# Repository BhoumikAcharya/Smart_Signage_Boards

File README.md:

**Modbus-to-MQTT Bridge for Metro Emergency Signage**

> **Reconciled 2026-08-07** against Gateway `Pi.py` v2.0.0 and ESP32 `Firmware.ino` v3.0.0.
> The previous revision (2026-02-17) predated the relay → MOSFET redesign and described hardware and
> a control protocol that no longer exist. See `Embedded/ESP32/DOC_UPDATES_PENDING.md` §10.

**Authoritative documents** — this README is an orientation page; each of these is the source of truth for its area:

| Area | Document |
| --- | --- |
| PLC / SCADA integration | [`Embedded/RaspberryPi/Gateway/SCADA_Integration_Guide.md`](Embedded/RaspberryPi/Gateway/SCADA_Integration_Guide.md) |
| Gateway internals | [`Embedded/RaspberryPi/Gateway/Gateway_doc.md`](Embedded/RaspberryPi/Gateway/Gateway_doc.md) |
| Platform / deployment | [`Embedded/RaspberryPi/pi_agent.md`](Embedded/RaspberryPi/pi_agent.md) |
| ESP32 firmware contract | [`Embedded/ESP32/esp32_contract.md`](Embedded/ESP32/esp32_contract.md) |
| HMI | [`Embedded/RaspberryPi/HMI/hmi_contract.md`](Embedded/RaspberryPi/HMI/hmi_contract.md) |

---

1. Overview Of the Product -

  This project is a smart EROS, designed for reliable operation in public transit environments like metros and railways. It implements a robust communication bridge on a Raspberry Pi, designed to integrate a central industrial control system (using Modbus) with a distributed network of emergency signs (using MQTT), all over **wired Ethernet**. Making the product implemented on a complete local network.

  This architecture allows a PLC or a central control room to instantly and reliably activate or change emergency signage across multiple locations in a station or tunnel, using a combination of industrial-grade protocols and modern IoT technology.

> **There is no wireless link anywhere in this system.** Every ESP32 node reaches the gateway over
> wired Ethernet via a LAN8720 PHY. The nodes have no Wi-Fi credentials and no Wi-Fi code path — the
> ESP32's radio is left off, which is also why only ADC1 is usable for the sensors.

2. System Architecture

  The project is built on a decoupled, hub-and-spoke architecture, which is ideal for critical systems:

  Central Control (PLC/Modbus Master): The primary industrial controller, located in a central control room. It initiates commands by sending standard Modbus "Write Multiple Holding Registers (16(0x10))" requests to the Raspberry Pi.

  2.1. Raspberry Pi (The Bridge & Broker): This is the core of the system and performs three critical roles simultaneously.

  2.2. Modbus TCP Server: A Python script runs continuously, listening for commands from the central controller and updating an internal data model.

  2.3. MQTT Broker: The industry-standard Mosquitto broker runs as a service, managing all communication with the signage units.

  2.4. Industrial HMI: A 10.1" capacitive touch HMI (Waveshare DSI, 1280x800) is connected to the RaspberryPi with manual override.

  2.5. Emergency Signs (ESP32 Clients): Each emergency light signage unit is powered by an ESP32.

  2.6. The ESP32s connect to the Raspberry Pi over Ethernet with a ETH PHY module called the LAN8720 with MQTT communication.

  2.7. They subscribe to specific MQTT topics and wait for commands.

  2.8. They are responsible for the final physical action — driving the LED strips through **10 logic-level N-channel MOSFETs**, switched over I2C by an MCP23017 port expander.

> **The relays are gone.** Earlier revisions of the design switched the signage with 5V dual-channel
> relay modules on GPIO 4/13, and the ESP32 toggled a GPIO directly. The current hardware has no
> relays: the ESP32 talks I2C to an MCP23017 (SDA=GPIO4, SCL=GPIO13) which drives 10 MOSFET gates —
> 5 for the left-hand arrows (Port A0–A4) and 5 for the right (Port B0–B4).
>
> **Only the moving arrows are switched.** The two static zones are hardwired always-on: they are
> current-monitored but can never be commanded on or off.

3. Features -

  3.1. Protocol Bridging: Seamlessly translates industrial-grade Modbus TCP commands into lightweight MQTT messages suitable for the edge nodes.

  3.2. Real-Time, Reliable Control: Uses a multi-threaded approach on the Raspberry Pi to ensure low latency between receiving a Modbus command and publishing the corresponding MQTT message.

  3.3. Scalable: Easily add or remove signage units across a station without any changes to the central controller or bridge logic. The register map is fixed at **100 nodes** (`40001`–`40100`); each sign only needs to know the broker's address and its own register number.

  3.4. Decoupled & Robust: The central controller does not need to know anything about the individual signs, and the signs do not need to know about the controller. This separation makes the system highly reliable and easy to maintain.

  3.5. Custom Logic: The bridge script contains specific control logic, allowing complex actions to be easily implemented.

  3.6. Diagnostics data: Diagnostics data of the LEDs, ESP32 and PSU Failure are communicated through MQTT to the RaspberryPi. Rather than a binary OK/FAIL, each of the four current channels reports a **4-state** value — `ON`, `OFF`, `FAIL_OPEN` (intended on, no current: burnt LED or blown MOSFET) or `FAIL_SHORT` (intended off, current flowing).

  3.7. Commanded vs Actual: Each node publishes what it is **actually executing**, not just what it was told. A node that cannot verify its own outputs reports a hardware fault that cannot be cleared by commanding anything. This is the system's most serious alarm — see the integration guide.

  3.8. Battery diagnostics are **still in development**. The firmware deliberately publishes nothing for battery, and the gateway reports `65535` = unknown. It is never reported as `0%`, which would be indistinguishable from a genuinely flat battery. **SCADA must not alarm on it.**

4. Hardware Components -

  This is the list of components that i have used (feel free to experiment on your own as well)

    Raspberry Pi 5(8GB RAM with Ethernet)

    ESP32 Development Board (DevKit 1)

    LAN8720 ETH PHY Module for the ESP32

    4x ACS712 Current Sensor — 5A parts on the two arrow channels, 20A on the two static zones

    MCP23017 I2C port expander (address 0x20)

    10x logic-level N-channel MOSFETs (100R gate series, 10k pull-down)

    4x MP1584 buck converter (3x 12V LED rails + 1x 5V), AMS1117-3.3 for the 3.3V rail

    12V LED strips — 5x left arrow, 5x right arrow, 2x static zone

    PLC or Modbus Master Simulator (like OpenModscan) for testing

    14.5V PSU (Preferrably a battery charger w/o XT60 connectors)

    12.8V LFP Battery (For ample battery backup)

    10.1" Waveshare DSI Capacitive Touch Display for HMI (1280x800)

> Wiring detail lives in `PCB/PCB_V3/Connections.md`, but **the finalized pin map is
> `Embedded/ESP32/esp32_contract.md` §1**, which supersedes it where they disagree.

5. Software & Libraries -

  5.1. Raspberry Pi:

    Raspberry Pi OS (Debian 13)

  Python 3

    Mosquitto 2.0.21 (MQTT Broker)

    pymodbus **3.11.3** (Python Modbus Library)

    paho-mqtt **2.1.0** (Python MQTT Client Library), `CallbackAPIVersion.VERSION2`

> **These versions are pinned, not incidental.** pymodbus 3.14 removes the datastore API this bridge
> is built on, and paho 1.x callback signatures fail outright on 2.x. See `pi_agent.md` §6–§7 before
> upgrading anything.

  5.2. ESP32:

    Arduino IDE or PlatformIO

    PubSubClient (Arduino MQTT Library)

    Adafruit_MCP23X17 (I2C port expander)

  5.3. Modbus Master:

    OpenModscan (For testing the control values in the Holding Registers of the PLC)

6. How It Works

  The central control room's PLC sends a Modbus command — a mode value written into a holding register in the SCADA buffer (`42001`–`42100`, one per node) — to the Raspberry Pi's IP address on port 502.

  The Python Modbus server script running on the Pi receives the command and updates its internal datastore.

  A dedicated "bridge" thread in the script detects this state change. Depending on the MUX flag (`43001`), it copies either the SCADA buffer or the HMI buffer into the active execution zone (`40001+`).

  The script, acting as an MQTT client, connects to the local Mosquitto broker and publishes the register's integer **verbatim** to that node's topic — for example node 1 receives payload `1` on `metro/signage/register/40001/value`.

  The Mosquitto broker forwards this message to the sign subscribed to that topic.

  The target ESP32 receives the value, decodes it, and executes the physical action — writing the corresponding bit pattern to the MCP23017, which switches the MOSFET gates driving the LED strips. The write is **read back and verified** before the node reports the mode as executing.

**Command values:**

| Value | Meaning |
| --- | --- |
| `0` / `1` / `2` | Arrows OFF / LHS chase / RHS chase (operator) |
| `3` | Both chase (technician) |
| `4` / `5` / `6` | Solid ON left / right / all (technician) |
| `10000`–`11023` | Raw 10-bit MOSFET bitmask, `value − 10000` (technician) |

> **The topic address is the holding-register number (`40001 + i`), not the node index.** Node 1 is
> `register/40001/value`. Get this wrong and the node reads OFFLINE with no error logged anywhere.
>
> **On network loss a node holds its last command** and keeps animating — there is no fail-safe timer
> and no forced ON/OFF state. Note that this survives a link outage but **not** a reboot: NVS
> persistence is not yet implemented, so a node rebooting during an outage comes up dark.

7. Setup & Usage

7.1. Raspberry Pi Setup

  Install the broker:

```bash
sudo apt update && sudo apt install mosquitto mosquitto-clients python3-venv python3-tk -y
```

  Install the Python libraries. **PEP 668 is enforced on Debian 13 — a bare `pip3 install` is refused by the system Python.** Use a venv with `--system-site-packages` so it can also see the apt-installed Tkinter that the HMI needs:

```bash
python3 -m venv --system-site-packages ~/metro-gw/venv
source ~/metro-gw/venv/bin/activate
pip install paho-mqtt==2.1.0 pymodbus==3.11.3
```

  Set the static IPs of the RaspberryPi — `10.45.2.50` on the SCADA side and `192.168.1.10` on the ESP32 side. These are committed values, not examples. See `pi_agent.md` §9 for the NetworkManager profile and §10 for the Mosquitto drop-in config.

7.2. ESP32 Setup

  Open `Embedded/ESP32/Firmware/Firmware.ino` in the Arduino IDE.

  Set `ASSIGNED_REGISTER` for each board — node 1 is `40001`, node 2 is `40002`, and so on. This is the only per-node change; there are no Wi-Fi credentials to set, as the nodes are wired.

  Upload to each ESP32. Confirm on the serial monitor (115200 baud) that the MCP23017 is found on SDA=4 / SCL=13.

> Flash `Firmware_Test/Firmware_Test.ino` first to validate the hardware over serial with no network
> stack — see `Embedded/ESP32/Firmware_Test/README.md`. Production firmware also carries its own
> commissioning menu; press `h` on the serial console.

7.3. Running the Bridge

```bash
source ~/metro-gw/venv/bin/activate
python3 Embedded/RaspberryPi/Gateway/Pi.py
```

  Port 502 is privileged. **Do not run the bridge as root** — keep the daemon unprivileged and grant only the one capability it needs, via the systemd unit in `Embedded/RaspberryPi/Gateway/deploy/`:

```ini
AmbientCapabilities=CAP_NET_BIND_SERVICE
Restart=always
```

  Keep the Gateway and the HMI as **two separate systemd units**. The decoupling exists so an HMI crash cannot take down the SCADA-facing Modbus server.

  The system is now live. Commands sent from the PLC will be relayed over Ethernet to the emergency signs.

> **You can exercise the whole gateway and HMI with zero ESP32 hardware** using
> `Embedded/RaspberryPi/Gateway/bench/simulate_node.py` and `scada_probe.py`. See `pi_agent.md` §13.

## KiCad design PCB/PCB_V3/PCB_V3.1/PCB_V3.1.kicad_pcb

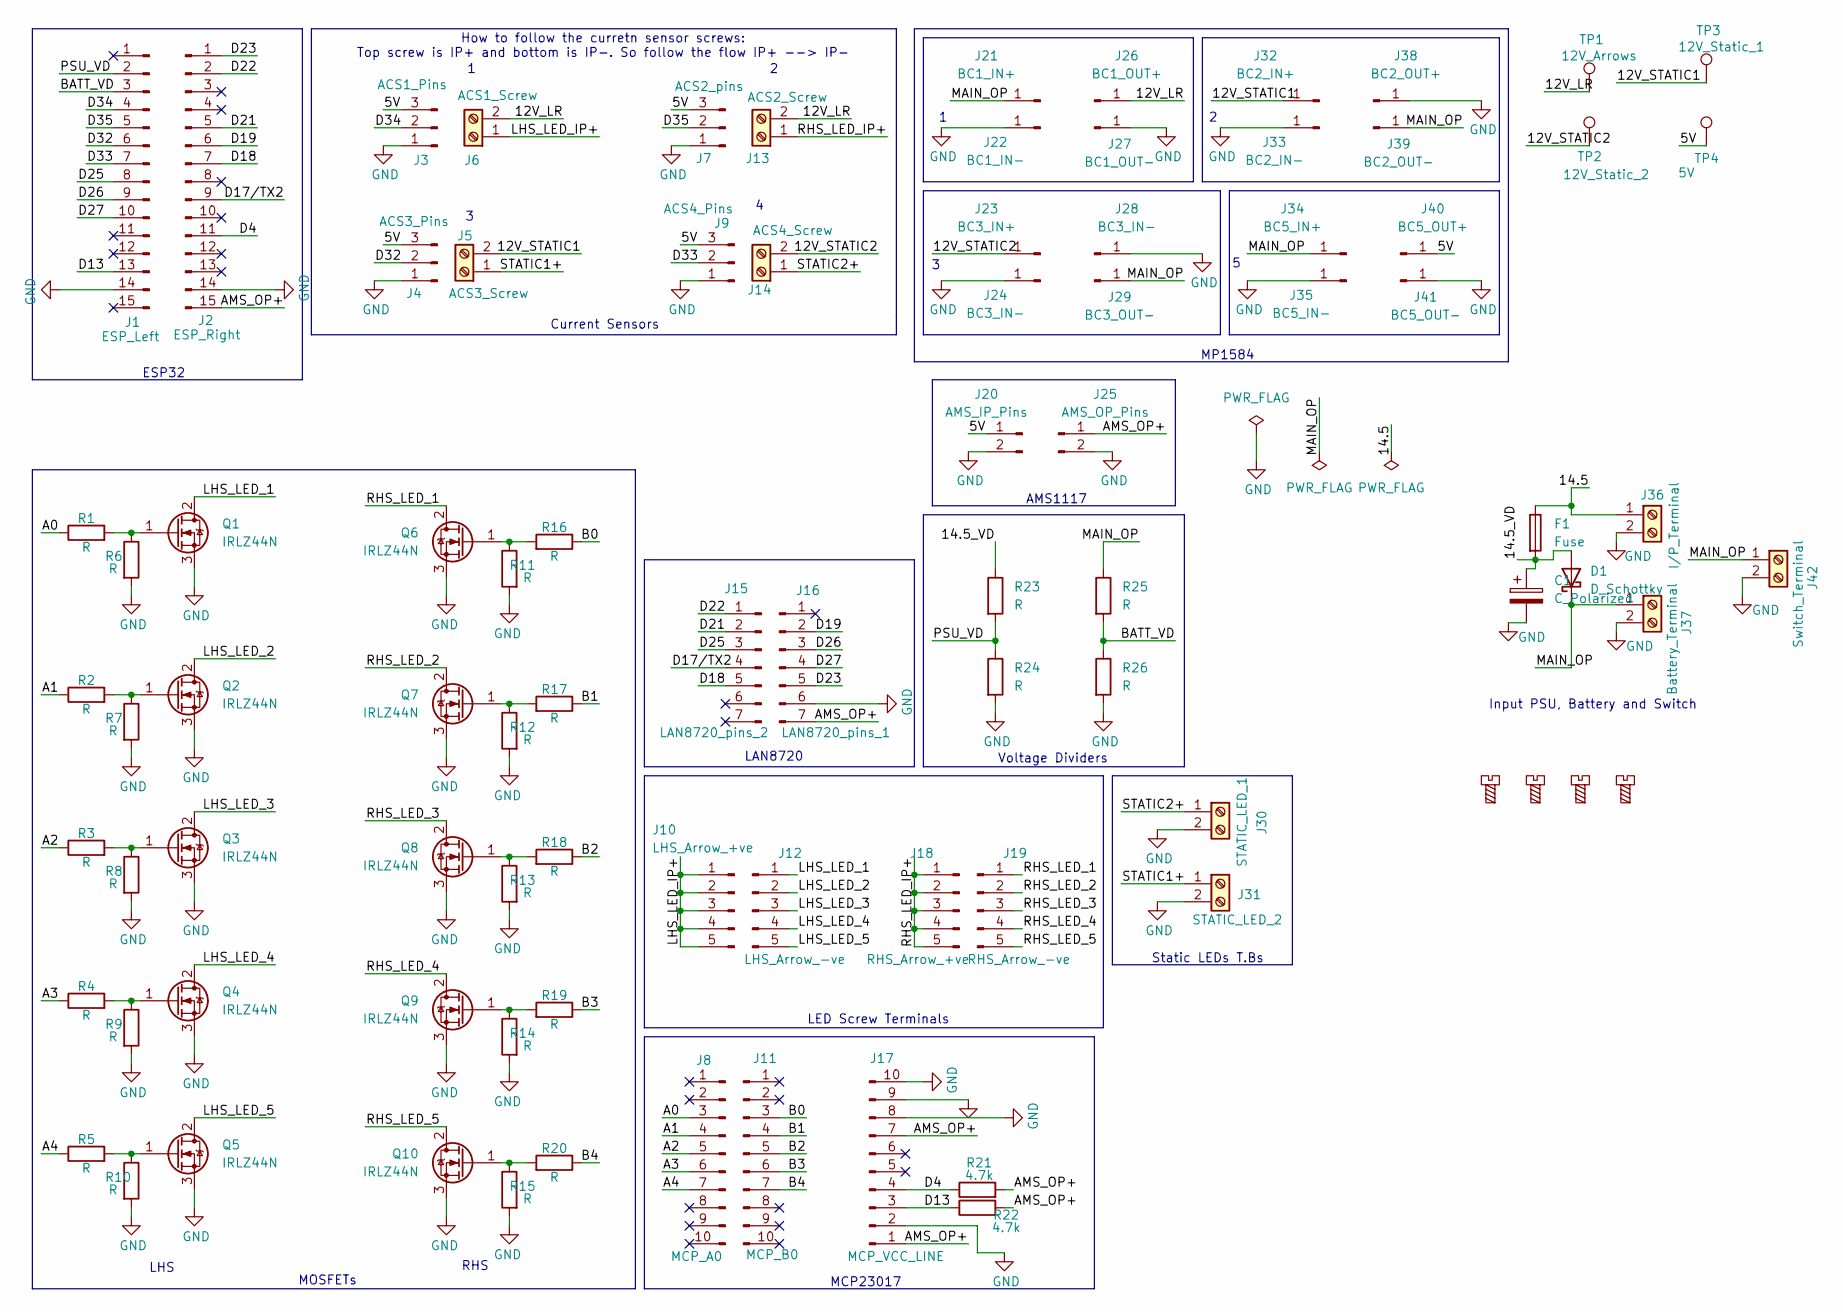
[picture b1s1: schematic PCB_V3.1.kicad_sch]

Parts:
C1: C_Polarized; CP_Radial_D10.0mm_P5.00mm
D1: D_Schottky; TO-220-2_Vertical
F1: Fuse; Fuseholder_BF020_21.3mmm
H1, H2, H3, H4: MountingScrew; MountingHole_4.3mm_M4
J1: ESP_Left; PinHeader_1x15_P2.54mm_Vertical
J2: ESP_Right; PinHeader_1x15_P2.54mm_Vertical
J3: ACS1_Pins; PinSocket_1x03_P2.54mm_Vertical
J4: ACS3_Pins; PinSocket_1x03_P2.54mm_Vertical
J5: ACS3_Screw; TerminalBlock_Phoenix_MKDS-1,5-2-5.08_1x02_P5.08mm_Horizont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
J6: ACS1_Screw; TerminalBlock_Phoenix_MKDS-1,5-2-5.08_1x02_P5.08mm_Horizont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
J7: ACS2_pins; PinHeader_1x03_P2.54mm_Vertical
J8: MCP_A0; PinSocket_1x10_P2.54mm_Vertical
J9: ACS4_Pins; PinSocket_1x03_P2.54mm_Vertical
J10: LHS_Arrow_+ve; PinSocket_1x05_P2.54mm_Vertical
J11: MCP_B0; PinSocket_1x10_P2.54mm_Vertical
J12: LHS_Arrow_-ve; PinSocket_1x05_P2.54mm_Vertical
J13: ACS2_Screw; TerminalBlock_Phoenix_MKDS-1,5-2-5.08_1x02_P5.08mm_Horizont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
J14: ACS4_Screw; TerminalBlock_Phoenix_MKDS-1,5-2-5.08_1x02_P5.08mm_Horizont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
J15: LAN8720_pins_2; PinSocket_1x07_P2.54mm_Vertical
J16: LAN8720_pins_1; PinSocket_1x07_P2.54mm_Vertical
J17: MCP_VCC_LINE; PinSocket_1x10_P2.54mm_Vertical
J18: RHS_Arrow_+ve; PinSocket_1x05_P2.54mm_Vertical
J19: RHS_Arrow_-ve; PinSocket_1x05_P2.54mm_Vertical
J20: AMS_IP_Pins; PinSocket_1x02_P2.54mm_Vertical
J21: BC1_IN+; PinSocket_1x01_P2.54mm_Vertical
J22: BC1_IN-; PinSocket_1x01_P2.54mm_Vertical
J23: BC3_IN+; PinSocket_1x01_P2.54mm_Vertical
J24, J28: BC3_IN-; PinSocket_1x01_P2.54mm_Vertical
J25: AMS_OP_Pins; PinSocket_1x02_P2.54mm_Vertical
J26: BC1_OUT+; PinSocket_1x01_P2.54mm_Vertical
J27: BC1_OUT-; PinSocket_1x01_P2.54mm_Vertical
J29: BC3_OUT-; PinSocket_1x01_P2.54mm_Vertical
J30: STATIC_LED_1; TerminalBlock_Phoenix_MKDS-1,5-2-5.08_1x02_P5.08mm_Horizont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
J31: STATIC_LED_2; TerminalBlock_Phoenix_MKDS-1,5-2-5.08_1x02_P5.08mm_Horizont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
J32: BC2_IN+; PinSocket_1x01_P2.54mm_Vertical
J33: BC2_IN-; PinSocket_1x01_P2.54mm_Vertical
J34: BC5_IN+; PinSocket_1x01_P2.54mm_Vertical
J35: BC5_IN-; PinSocket_1x01_P2.54mm_Vertical
J36: I/P_Terminal; TerminalBlock_Phoenix_MKDS-1,5-2-5.08_1x02_P5.08mm_Horizont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
J37: Battery_Terminal; TerminalBlock_Phoenix_MKDS-1,5-2-5.08_1x02_P5.08mm_Horizont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
J38: BC2_OUT+; PinSocket_1x01_P2.54mm_Vertical
J39: BC2_OUT-; PinSocket_1x01_P2.54mm_Vertical
J40: BC5_OUT+; PinSocket_1x01_P2.54mm_Vertical
J41: BC5_OUT-; PinSocket_1x01_P2.54mm_Vertical
J42: Switch_Terminal; TerminalBlock_Phoenix_MKDS-1,5-2-5.08_1x02_P5.08mm_Horizont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
Q1, Q2, Q3, Q4, Q5, Q6, Q7, Q8, Q9, Q10: IRLZ44N; TO-220-3_Vertical
R1, R2, R3, R4, R5, R6, R7, R8, R9, R10, R11, R12, R13, R14, R15, R16, R17, R18, R19, R20, R23, R24, R25, R26: R; R_Axial_DIN0207_L6.3mm_D2.5mm_P10.16mm_Horizontal
R21, R22: 4.7k; R_Axial_DIN0207_L6.3mm_D2.5mm_P10.16mm_Horizontal
TP1: 12V_Arrows; TestPoint_Pad_D1.5mm
TP2: 12V_Static_2; TestPoint_Pad_D1.5mm
TP3: 12V_Static_1; TestPoint_Pad_D1.5mm
TP4: 5V; TestPoint_Pad_D1.5mm

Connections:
/5V: J3.3, J4.3, J7.3, J9.3, J20.1, J40.1 (Pin_1_1), TP4.1 (1_1)
/12V_LR: J6.2, J13.2, J26.1 (Pin_1_1), TP1.1 (1_1)
/12V_STATIC1: J5.2, J32.1 (Pin_1_1), TP3.1 (1_1)
/12V_STATIC2: J14.2, J23.1 (Pin_1_1), TP2.1 (1_1)
/14.5: F1.1, J36.1
/14.5_VD: C1.1, D1.2 (A), F1.2, R23.1
/A0: J8.3, R1.1
/A1: J8.4, R2.1
/A2: J8.5, R3.1
/A3: J8.6, R4.1
/A4: J8.7, R5.1
/AMS_OP+: J2.15, J16.7, J17.1, J17.7, J25.1, R21.2, R22.2
/B0: J11.3, R16.1
/B1: J11.4, R17.1
/B2: J11.5, R18.1
/B3: J11.6, R19.1
/B4: J11.7, R20.1
/BATT_VD: J1.3, R25.2, R26.1
/D4: J2.11, J17.4, R21.1
/D13: J1.13, J17.3, R22.1
/D17/TX2: J2.9, J15.4
/D18: J2.7, J15.5
/D19: J2.6, J16.2
/D21: J2.5, J15.2
/D22: J2.2, J15.1
/D23: J2.1, J16.5
/D25: J1.8, J15.3
/D26: J1.9, J16.3
/D27: J1.10, J16.4
/D32: J1.6, J4.2
/D33: J1.7, J9.2
/D34: J1.4, J3.2
/D35: J1.5, J7.2
/LHS_LED_1: J12.1, Q1.2 (D)
/LHS_LED_2: J12.2, Q2.2 (D)
/LHS_LED_3: J12.3, Q3.2 (D)
/LHS_LED_4: J12.4, Q4.2 (D)
/LHS_LED_5: J12.5, Q5.2 (D)
/LHS_LED_IP+: J6.1, J10.1, J10.2, J10.3, J10.4, J10.5
/MAIN_OP: D1.1 (K), J21.1 (Pin_1_1), J29.1 (Pin_1_1), J34.1 (Pin_1_1), J37.1, J39.1 (Pin_1_1), J42.1, R25.1
/PSU_VD: J1.2, R23.2, R24.1
/RHS_LED_1: J19.1, Q6.2 (D)
/RHS_LED_2: J19.2, Q7.2 (D)
/RHS_LED_3: J19.3, Q8.2 (D)
/RHS_LED_4: J19.4, Q9.2 (D)
/RHS_LED_5: J19.5, Q10.2 (D)
/RHS_LED_IP+: J13.1, J18.1, J18.2, J18.3, J18.4, J18.5
/STATIC1+: J5.1, J31.1
/STATIC2+: J14.1, J30.1
GND: C1.2, J1.14, J2.14, J3.1, J4.1, J7.1, J9.1, J16.6, J17.2, J17.8, J17.9, J17.10, J20.2, J22.1 (Pin_1_1), J24.1 (Pin_1_1), J25.2, J27.1 (Pin_1_1), J28.1 (Pin_1_1), J30.2, J31.2, J33.1 (Pin_1_1), J35.1 (Pin_1_1), J36.2, J37.2, J38.1 (Pin_1_1), J41.1 (Pin_1_1), J42.2, Q1.3 (S), Q2.3 (S), Q3.3 (S), Q4.3 (S), Q5.3 (S), Q6.3 (S), Q7.3 (S), Q8.3 (S), Q9.3 (S), Q10.3 (S), R6.2, R7.2, R8.2, R9.2, R10.2, R11.2, R12.2, R13.2, R14.2, R15.2, R24.2, R26.2
unnamed: Q1.1 (G), R1.2, R6.1
unnamed: Q2.1 (G), R2.2, R7.1
unnamed: Q3.1 (G), R3.2, R8.1
unnamed: Q4.1 (G), R4.2, R9.1
unnamed: Q5.1 (G), R5.2, R10.1
unnamed: Q6.1 (G), R11.1, R16.2
unnamed: Q7.1 (G), R12.1, R17.2
unnamed: Q8.1 (G), R13.1, R18.2
unnamed: Q9.1 (G), R14.1, R19.2
unnamed: Q10.1 (G), R15.1, R20.2

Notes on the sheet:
MP1584
ESP32
Voltage Dividers
How to follow the curretn sensor screws: Top screw is IP+ and bottom is IP-. So follow the flow IP+ --> IP-
LAN8720
Input PSU, Battery and Switch
MOSFETs
RHS
LED Screw Terminals
AMS1117
LHS
Current Sensors
Static LEDs T.Bs
MCP23017

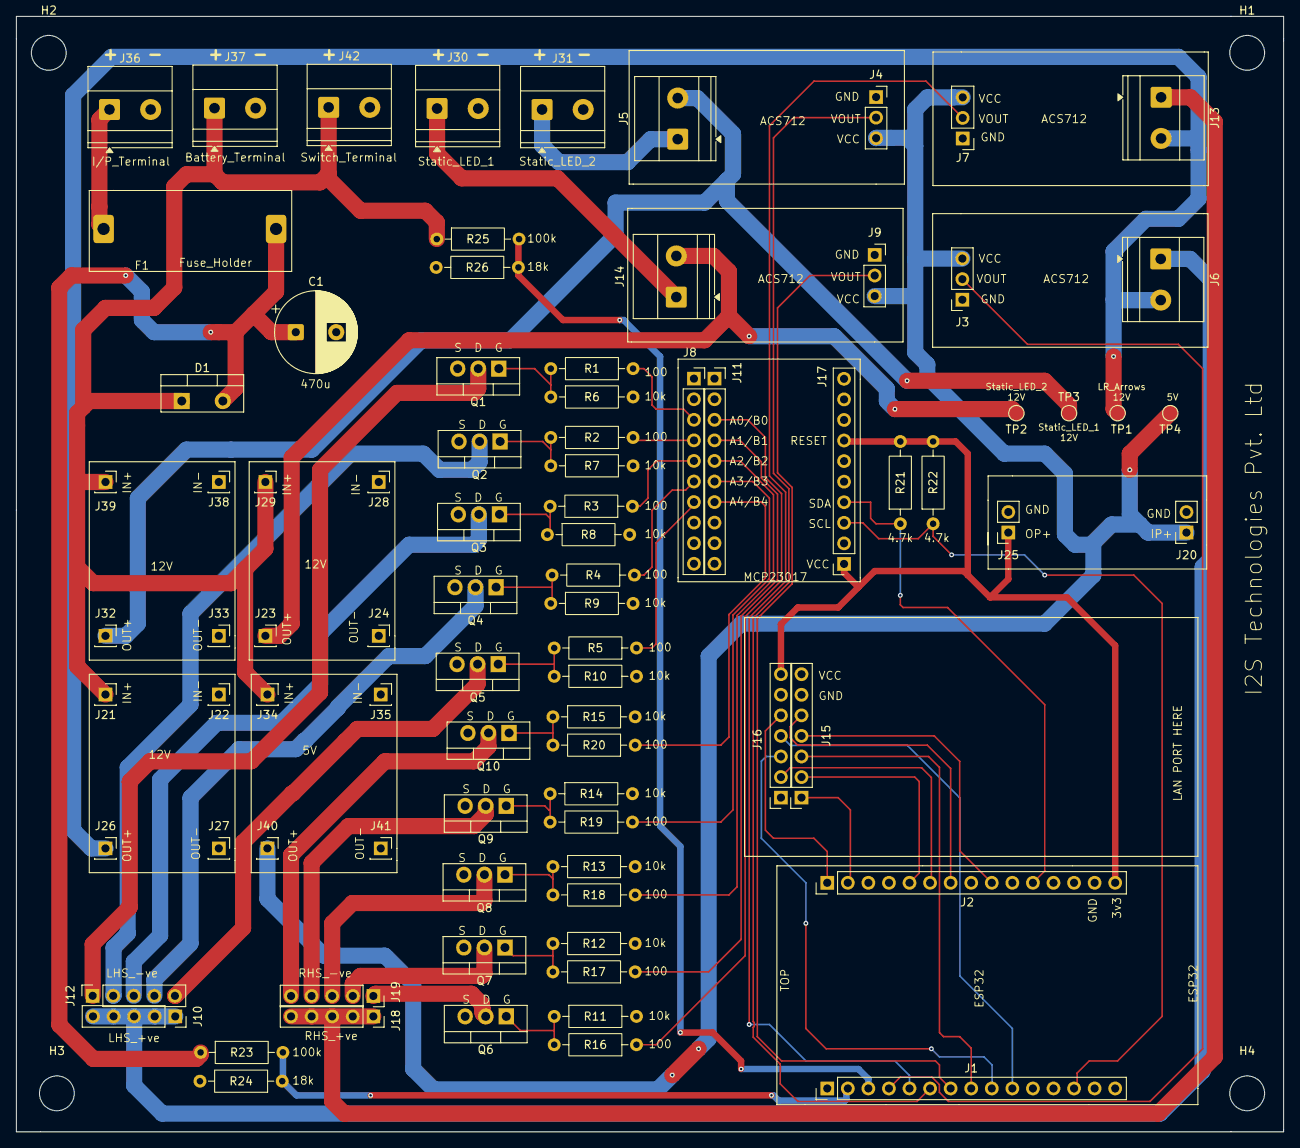
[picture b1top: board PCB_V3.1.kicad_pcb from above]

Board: 2 copper layers, 156.5 x 137.8 mm, 89 parts (0 on the bottom side), 60 nets.

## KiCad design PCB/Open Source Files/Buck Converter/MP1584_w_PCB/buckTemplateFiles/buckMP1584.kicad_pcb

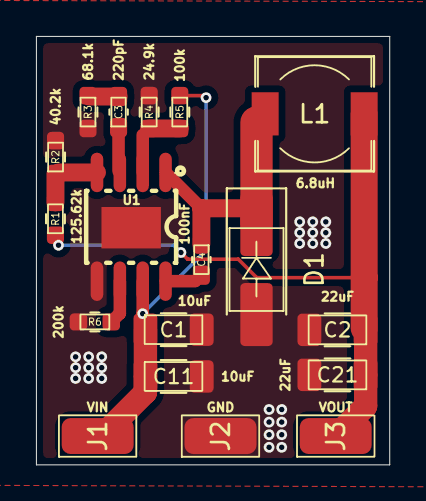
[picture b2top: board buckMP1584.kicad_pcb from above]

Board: 2 copper layers, 19.6 x 23.8 mm, 18 parts (0 on the bottom side), 10 nets.

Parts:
C1, C11: 10uF; C_1206_3216Metric_Pad1.33x1.80mm_HandSolder
C2, C21: 22uF; C_1206_3216Metric_Pad1.33x1.80mm_HandSolder
C3: 220pF; C_0603_1608Metric_Pad1.08x0.95mm_HandSolder
C4: 100nF; C_0603_1608Metric_Pad1.08x0.95mm_HandSolder
D1: D_SMA_Handsoldering
J1: VIN; SolderWirePad_1x01_SMD_2x4mm
J2: GND; SolderWirePad_1x01_SMD_2x4mm
J3: VOUT; SolderWirePad_1x01_SMD_2x4mm
L1: 6.8uH; L_6.3x6.3_H3
R1: 125.62k; R_0603_1608Metric_Pad0.98x0.95mm_HandSolder
R2: 40.2k; R_0603_1608Metric_Pad0.98x0.95mm_HandSolder
R3: 68.1k; R_0603_1608Metric_Pad0.98x0.95mm_HandSolder
R4: 24.9k; R_0603_1608Metric_Pad0.98x0.95mm_HandSolder
R5: 100k; R_0603_1608Metric_Pad0.98x0.95mm_HandSolder
R6: 200k; R_0603_1608Metric_Pad0.98x0.95mm_HandSolder
U1: MP1584EN; SOIC-8_L4.9-W3.9-P1.27-LS6.0-BL-EP3.3

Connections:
+3.3V: C2.1, C21.1, J3.1 (Pin_1_1), L1.2, R1.1
/MP1584EN Buck module/Feedback: R1.2, R2.1, U1.4 (FB)
/VIN: C1.1, C11.1, J1.1 (Pin_1_1), R5.1, U1.7 (VIN)
GND: C1.2, C2.2, C11.2, C21.2, D1.2 (A), J2.1 (Pin_1_1), R2.2, R3.2, R4.2, R6.2, U1.5 (GND), U1.9 (GND)
unnamed: C3.2, R3.1
unnamed: C4.1, D1.1 (K), L1.1, U1.1 (SW)
unnamed: C4.2, U1.8 (BST)
unnamed: C3.1, U1.3 (COMP)
unnamed: R4.1, R5.2, U1.2 (EN)
unnamed: R6.1, U1.6 (FREQ)

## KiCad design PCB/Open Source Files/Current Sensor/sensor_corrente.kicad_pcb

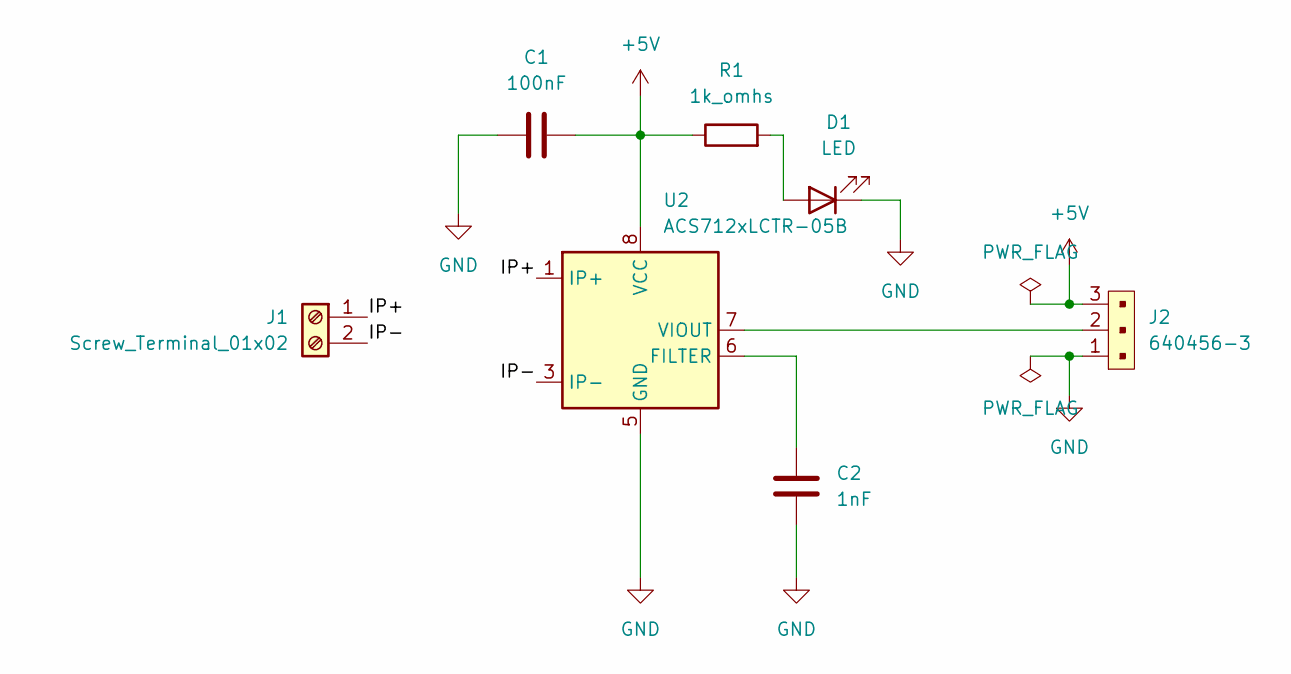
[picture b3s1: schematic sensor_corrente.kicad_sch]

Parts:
C1: 100nF; C_0805_2012Metric
C2: 1nF; C_0805_2012Metric
D1: LED; LED_0805_2012Metric
J1: Screw_Terminal_01x02; TerminalBlock_Phoenix_MKDS-1,5-2-5.08_1x02_P5.08mm_Horizont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
J2: 640456-3; PinHeader_1x3_P2.54_Drill1.1mm; MPN 640456-3; Digi-Key_PN A19470-ND
R1: 1k_omhs; R_0805_2012Metric
U2: ACS712xLCTR-05B; SOIC-8_3.9x4.9mm_P1.27mm

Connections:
+5V: C1.2, J2.3, R1.1, U2.8 (VCC)
/IP+: J1.1, U2.1 (IP+), U2.2 (IP+)
/IP-: J1.2, U2.3 (IP-), U2.4 (IP-)
GND: C1.1, C2.2, D1.1 (K), J2.1, U2.5 (GND)
unnamed: D1.2 (A), R1.2
unnamed: C2.1, U2.6 (FILTER)
unnamed: J2.2, U2.7 (VIOUT)

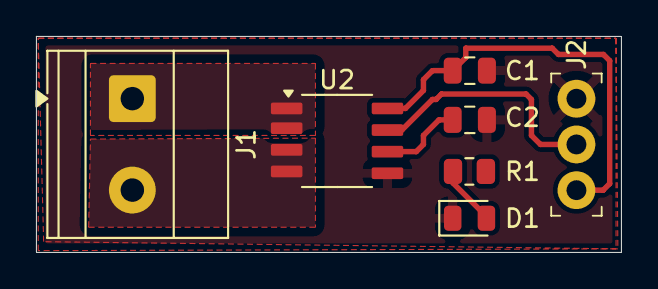
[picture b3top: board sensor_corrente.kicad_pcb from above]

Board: 2 copper layers, 32.5 x 12.0 mm, 7 parts (0 on the bottom side), 7 nets.

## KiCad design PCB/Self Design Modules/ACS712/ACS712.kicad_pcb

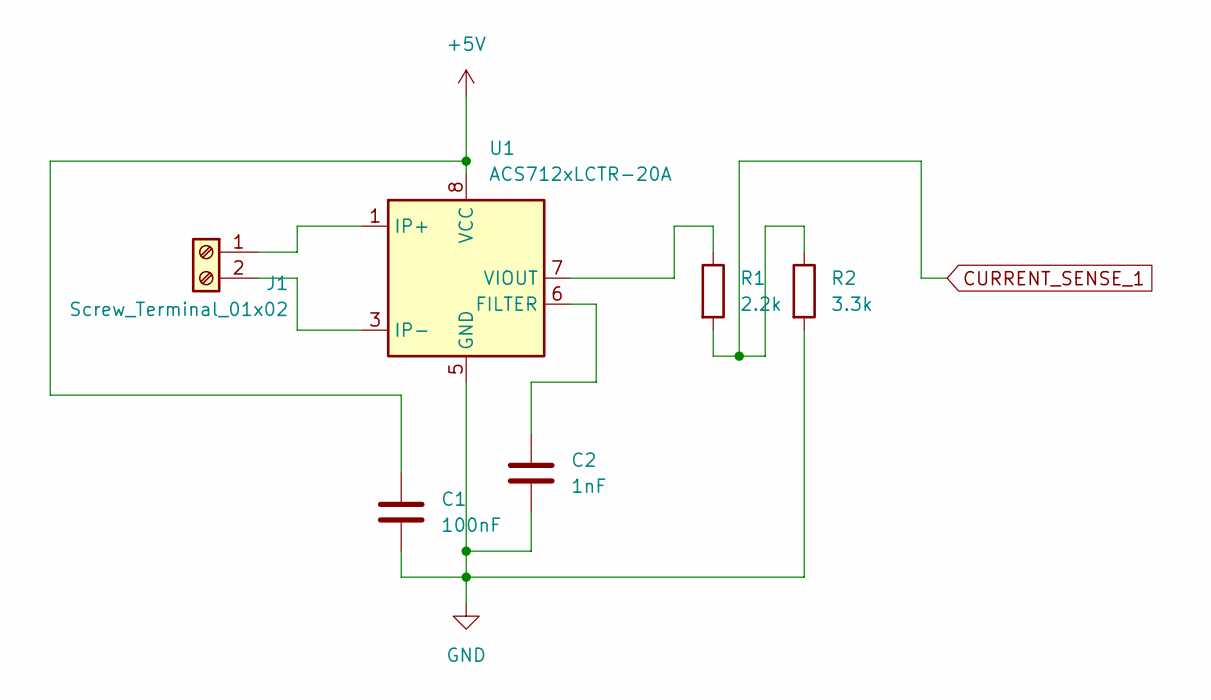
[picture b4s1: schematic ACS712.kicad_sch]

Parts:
C1: 100nF; C_0805_2012Metric
C2: 1nF; C_0805_2012Metric
J1: Screw_Terminal_01x02; TerminalBlock_Phoenix_MKDS-1,5-2-5.08_1x02_P5.08mm_Horizont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
R1: 2.2k; R_0805_2012Metric
R2: 3.3k; R_0805_2012Metric
U1: ACS712xLCTR-20A; SOIC-8_3.9x4.9mm_P1.27mm

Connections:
+5V: C1.1, U1.8 (VCC)
CURRENT_SENSE_1: R1.2, R2.1
GND: C1.2, C2.2, R2.2, U1.5 (GND)
unnamed: J1.1, U1.1 (IP+), U1.2 (IP+)
unnamed: J1.2, U1.3 (IP-), U1.4 (IP-)
unnamed: C2.1, U1.6 (FILTER)
unnamed: R1.1, U1.7 (VIOUT)

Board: 2 copper layers, 6 parts (0 on the bottom side), 7 nets, no tracks yet.

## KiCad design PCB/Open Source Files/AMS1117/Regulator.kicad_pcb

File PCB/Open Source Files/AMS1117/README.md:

📦 Repository Contents
Regulator.kicad_sch – KiCad schematic
Regulator.kicad_pcb – KiCad PCB layout
<br>

## Sponsored by PCBWay
This project sponsored by [PCBWay](https://www.pcbway.com), who supported the prototyping of this board.  
Special thanks to Liam from PCBWay’s marketing team for facilitating the collaboration.

## 🖼️ Previews

### Schematic

### PCB

### photos of the bare PCBs

### PCBWay Sponsorship & Quality Review

These boards were kindly sponsored by PCBWay

🟢 Quality: The PCBs arrived with sharp silkscreen, smooth edges, and consistent solder mask — even for the fine-pitch pads.

🟢 Service: Communication with the PCBWay team (special thanks to Liam 🙏) was very fast and helpful at every step.

🟢 Delivery: The shipping was reliable and the boards were safely packed.

I haven’t soldered components yet (waiting for my kit to arrive), but I’m already impressed with the build quality. Once assembly and testing are complete, I’ll share performance measurements and final photos.
**⚙️ Typical Specs (AMS1117-3.3 based) :**

Output: 3.3 V fixed

Input: (commonly) ≥ 4.5 V up to around 12 V (observe power dissipation!)

Dropout: ~1.1–1.3 V (load-dependent)

Max current: up to 1 A electrically, but thermally limited by SOT-223 and copper area

Thermal tip: Keep large copper under/around the tab (pin 2) for heat spreading; derate current for higher VIN–VOUT.

<br>
<br>

**🧠 How the Circuit Works :**

Input (J1) receives unregulated DC.

C1/C2 provide input bulk and high-frequency decoupling close to U1.IN.

U1 (AMS1117-3.3) regulates to 3.3 V at U1.OUT.

C3/C4 provide output bulk and HF bypass close to U1.OUT for stability and transient response.

LED D1 + R1 connect to the 3.3 V output as a power-good indicator.

Output (J2) provides the regulated 3.3 V and GND to your load.

<br>
<br>

**✨ Author:**

Awab — @AWABEEE

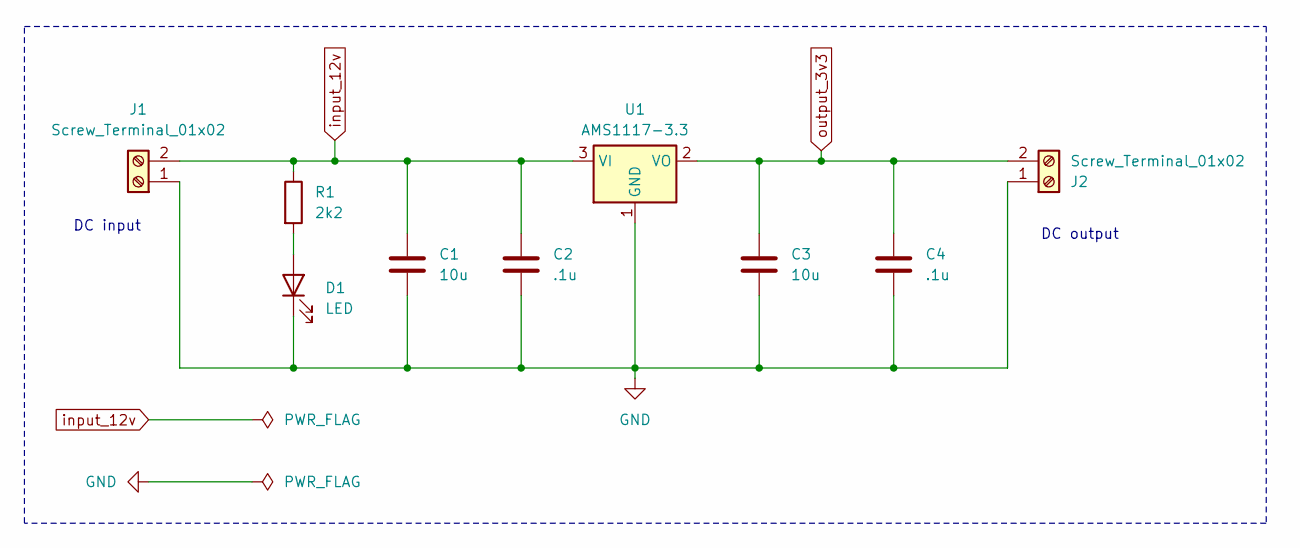
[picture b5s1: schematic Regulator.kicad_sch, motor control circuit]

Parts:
C1, C3: 10u; C_1206_3216Metric
C2, C4: .1u; C_0603_1608Metric
D1: LED; LED_1206_3216Metric
J1, J2: Screw_Terminal_01x02; TerminalBlock_bornier-2_P5.08mm
R1: 2k2; R_1206_3216Metric
U1: AMS1117-3.3; SOT-223-3_TabPin2

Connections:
GND: C1.2, C2.2, C3.2, C4.2, D1.1 (K), J1.1, J2.1, U1.1 (GND)
unnamed: D1.2 (A), R1.2
input_12v: C1.1, C2.1, J1.2, R1.1, U1.3 (VI)
output_3v3: C3.1, C4.1, J2.2, U1.2 (VO)

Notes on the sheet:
DC input
DC output

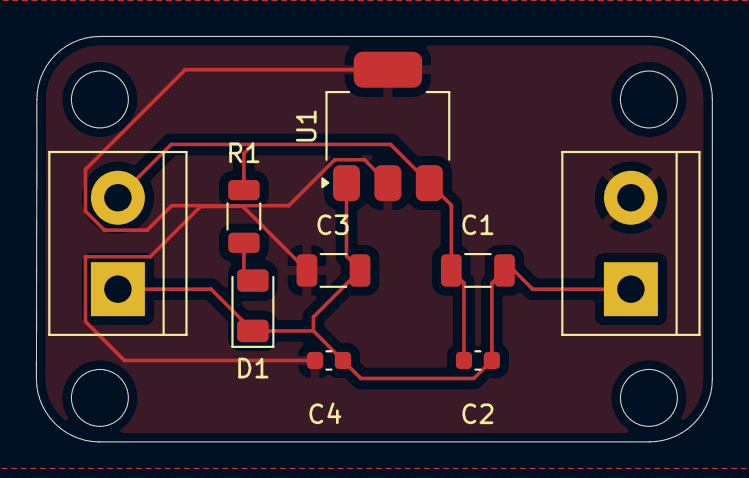
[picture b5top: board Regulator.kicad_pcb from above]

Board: 2 copper layers, 37.6 x 22.5 mm, 9 parts (0 on the bottom side), 4 nets.
